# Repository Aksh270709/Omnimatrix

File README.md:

# Omnimatrix
Once my friend told me about hackclub, as I was fascinated by the techinical world, I immediately joined hackclub. I learned Kicad, basic coding and other stuff. Then I attended an event of Hackclub, **Build Guild Delhi**. I explored various unique projects of different Hackclubbers, I was mesmerised by different project and also learned to build Macropad. Then, I started working on it. Firstly, I learned Kicad. I made many mistakes and took many learnings from them. Then finally, I started this project, Omnimatrix. One of the major reason to build this macropad is that, I love to edit videos, and also learning aminations. Editing consistently requires shortcuts like Copy, Paste, Split, Cut, etc. I wanted to simplify editing so, I planned to design it, I spent approx 2 hours on Schematic, 3-4 hours on PCB and 4-5 hours on Case and editing stuff. Also I took help from AI in order to edit the code because currently I don't have much experience in coding. In this project, I used XIAO RP2040-DIP, Mechanical keys (9x) and 1N4148 Diode (9x) etc. for my project. Initially I was confused and made many mistakes. But eventually I build my understanding and corrected those mistakes. It took more than 8 hours to make this project and also spent weeks to learn Kicad, Case designing stuff. After many failures and learnings, **Omnimatrix** a beginner friendly macropad which is easy to use as well as easy to build is finally completed.

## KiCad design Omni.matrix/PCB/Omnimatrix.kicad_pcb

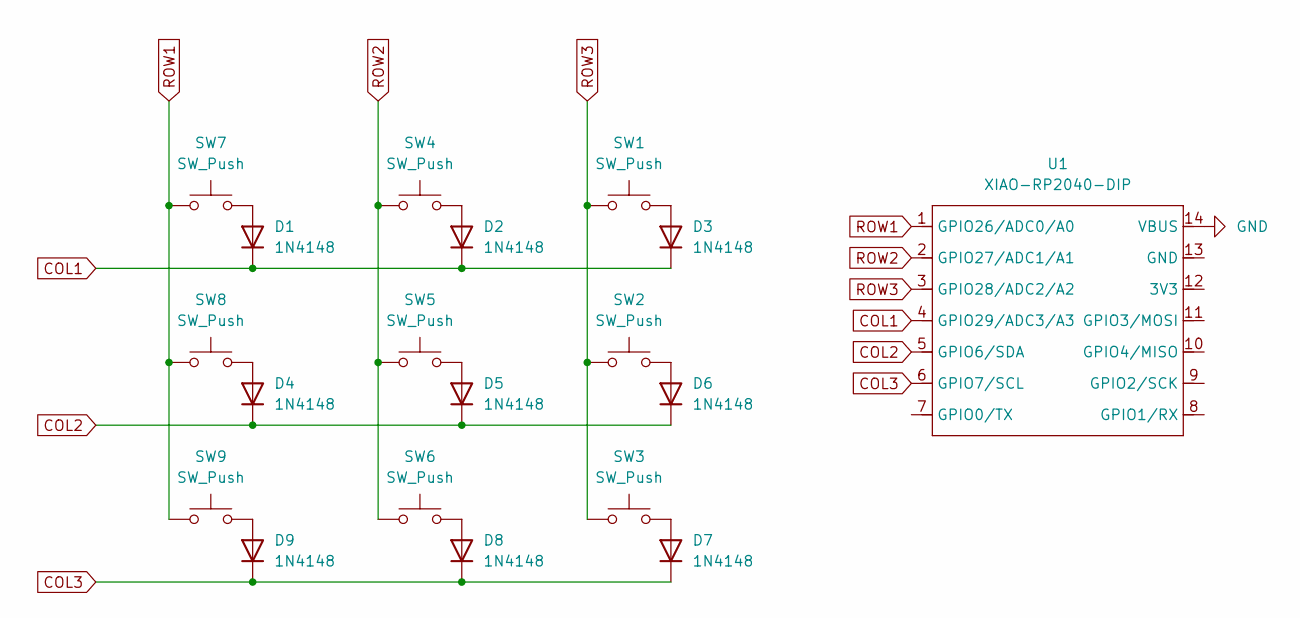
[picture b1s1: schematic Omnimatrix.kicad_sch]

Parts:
D1, D2, D3, D4, D5, D6, D7, D8, D9: 1N4148; D_DO-35_SOD27_P7.62mm_Horizontal
SW1, SW2, SW3, SW4, SW5, SW6, SW7, SW8, SW9: SW_Push; SW_Cherry_MX_1.00u_PCB
U1: XIAO-RP2040-DIP

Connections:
COL1: D1.1 (K), D2.1 (K), D3.1 (K), U1.4 (GPIO29/ADC3/A3)
COL2: D4.1 (K), D5.1 (K), D6.1 (K), U1.5 (GPIO6/SDA)
COL3: D7.1 (K), D8.1 (K), D9.1 (K), U1.6 (GPIO7/SCL)
GND: U1.14 (VBUS)
unnamed: D1.2 (A), SW7.2
unnamed: D2.2 (A), SW4.2
unnamed: D3.2 (A), SW1.2
unnamed: D4.2 (A), SW8.2
unnamed: D5.2 (A), SW5.2
unnamed: D6.2 (A), SW2.2
unnamed: D7.2 (A), SW3.2
unnamed: D8.2 (A), SW6.2
unnamed: D9.2 (A), SW9.2
ROW1: SW7.1, SW8.1, SW9.1, U1.1 (GPIO26/ADC0/A0)
ROW2: SW4.1, SW5.1, SW6.1, U1.2 (GPIO27/ADC1/A1)
ROW3: SW1.1, SW2.1, SW3.1, U1.3 (GPIO28/ADC2/A2)

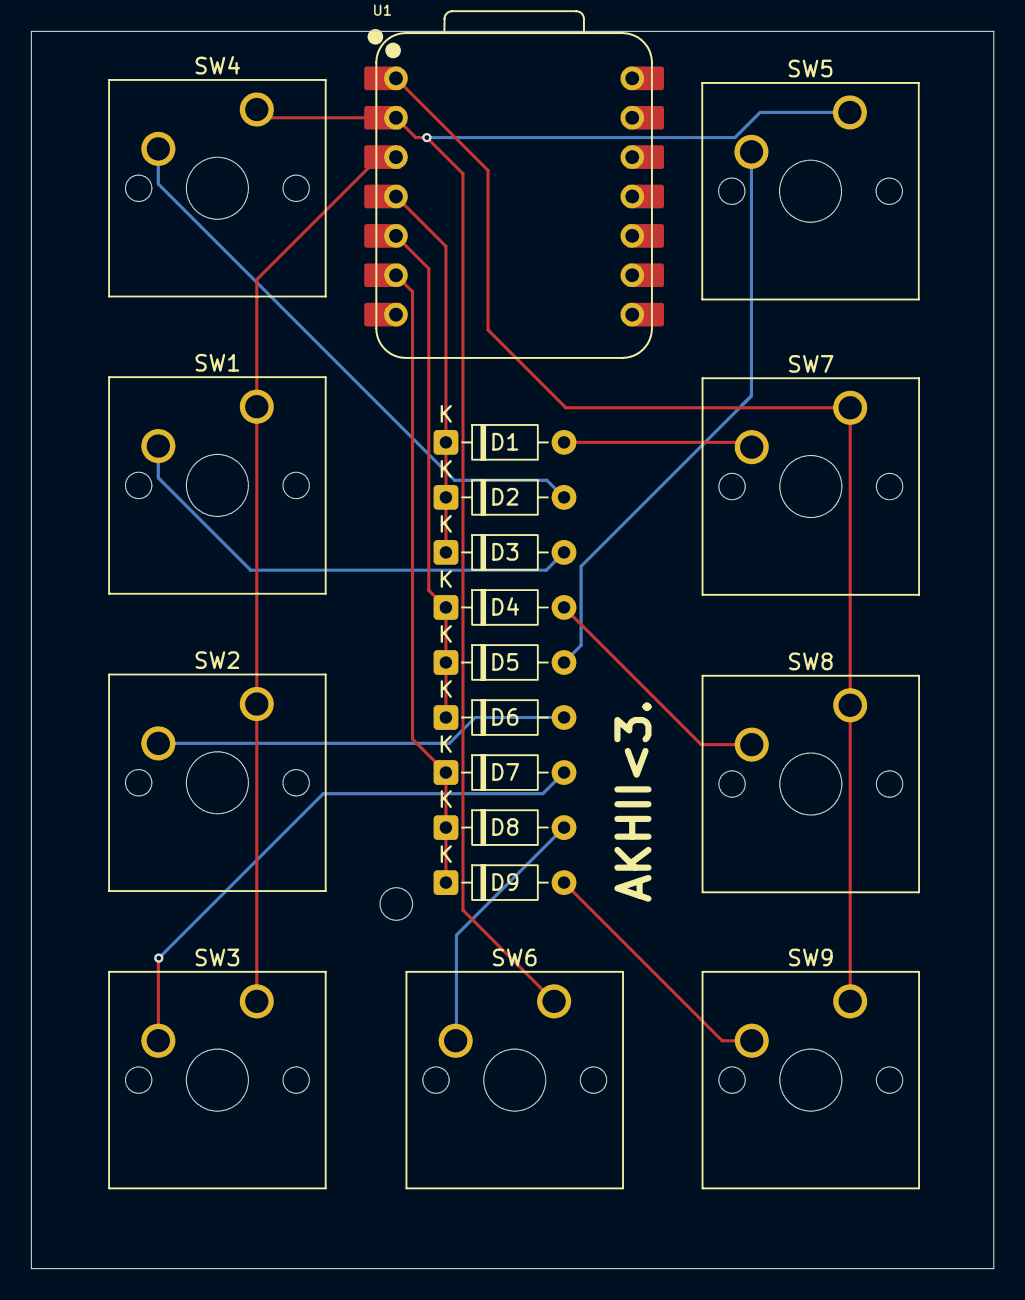
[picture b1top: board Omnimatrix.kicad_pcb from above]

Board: 2 copper layers, 62.1 x 79.8 mm, 19 parts (0 on the bottom side), 15 nets.

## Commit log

2026-06-20 Revise README with detailed project background
    Expanded project description and personal journey in README.
2026-06-20 Update README with additional project details
    Added information about AI assistance in coding.
